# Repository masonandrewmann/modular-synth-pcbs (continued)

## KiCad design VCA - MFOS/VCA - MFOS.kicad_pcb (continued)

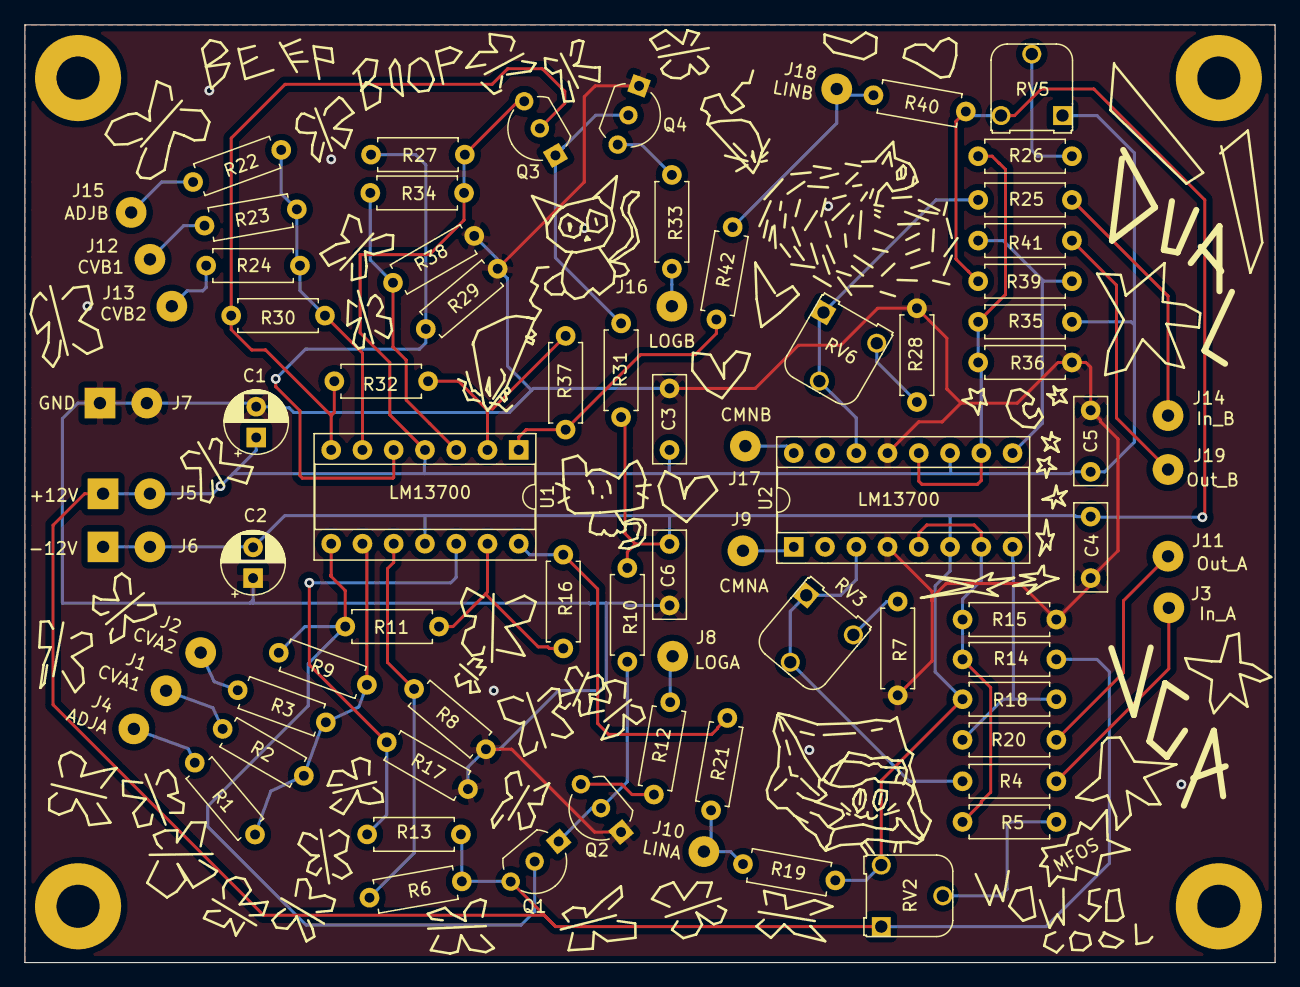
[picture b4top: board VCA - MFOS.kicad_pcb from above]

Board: 2 copper layers, 101.6 x 76.2 mm, 77 parts (0 on the bottom side), 45 nets.

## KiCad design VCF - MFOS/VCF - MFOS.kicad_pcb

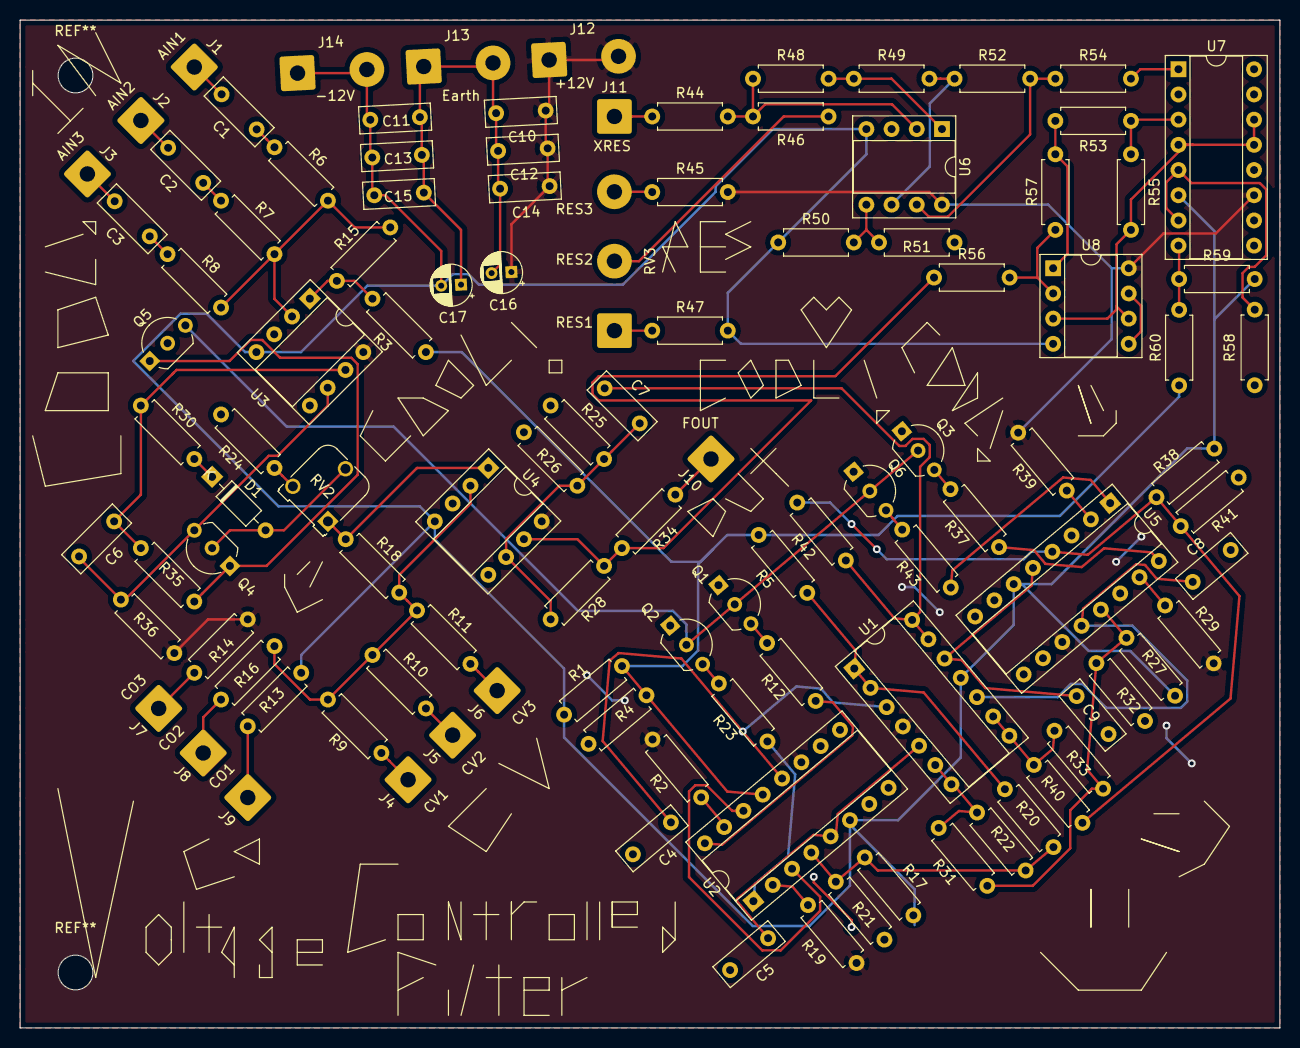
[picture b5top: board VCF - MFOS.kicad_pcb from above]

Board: 2 copper layers, 127.0 x 101.6 mm, 108 parts (0 on the bottom side), 69 nets.

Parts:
C1, C2, C3, C7, C10, C11, C12, C13, C14, C15: 0.1uF; C_Rect_L7.0mm_W2.5mm_P5.00mm
C4, C5, C6, C8, C9: 100pF; C_Rect_L7.0mm_W2.5mm_P5.00mm
C16, C17: 10uF; CP_Radial_D4.0mm_P2.00mm
D1: 1N914; D_DO-35_SOD27_P7.62mm_Horizontal
J1: AIN1; SolderWire-0.75sqmm_1x01_D1.25mm_OD3.5mm
J2: AIN2; SolderWire-0.75sqmm_1x01_D1.25mm_OD3.5mm
J3: AIN3; SolderWire-0.75sqmm_1x01_D1.25mm_OD3.5mm
J4: CV1; SolderWire-0.75sqmm_1x01_D1.25mm_OD3.5mm
J5: CV2; SolderWire-0.75sqmm_1x01_D1.25mm_OD3.5mm
J6: CV3; SolderWire-0.75sqmm_1x01_D1.25mm_OD3.5mm
J7: CO3; SolderWire-0.75sqmm_1x01_D1.25mm_OD3.5mm
J8: CO2; SolderWire-0.75sqmm_1x01_D1.25mm_OD3.5mm
J9: C01; SolderWire-0.75sqmm_1x01_D1.25mm_OD3.5mm
J10: FOUT; SolderWire-0.75sqmm_1x01_D1.25mm_OD3.5mm
J11: XRES; SolderWire-0.75sqmm_1x01_D1.25mm_OD3.5mm
J12: +12V; SolderWire-0.75sqmm_1x02_P7mm_D1.25mm_OD3.5mm
J13: GND; SolderWire-0.75sqmm_1x02_P7mm_D1.25mm_OD3.5mm
J14: -12V; SolderWire-0.75sqmm_1x02_P7mm_D1.25mm_OD3.5mm
Q1, Q2, Q3, Q6: 2N3906; TO-92_Inline_Wide
Q4, Q5: 2N3904; TO-92_Inline_Wide
R1, R13, R17: 39K; R_Axial_DIN0207_L6.3mm_D2.5mm_P7.62mm_Horizontal
R2, R19, R29, R39: 20K; R_Axial_DIN0207_L6.3mm_D2.5mm_P7.62mm_Horizontal
R3, R5, R9, R10, R11, R16, R20, R22, R26, R28, R31, R33, R40, R42, R44, R46, R49, R50, R52: 100K; R_Axial_DIN0207_L6.3mm_D2.5mm_P7.62mm_Horizontal
R4, R21, R32, R41: 100; R_Axial_DIN0207_L6.3mm_D2.5mm_P7.62mm_Horizontal
R6, R7, R8, R36: 1M; R_Axial_DIN0207_L6.3mm_D2.5mm_P7.62mm_Horizontal
R12, R23, R35, R37, R43: 10K; R_Axial_DIN0207_L6.3mm_D2.5mm_P7.62mm_Horizontal
R14: 33K; R_Axial_DIN0207_L6.3mm_D2.5mm_P7.62mm_Horizontal
R15: 390K; R_Axial_DIN0207_L6.3mm_D2.5mm_P7.62mm_Horizontal
R18, R34: 2K; R_Axial_DIN0207_L6.3mm_D2.5mm_P7.62mm_Horizontal
R24: 475; R_Axial_DIN0207_L6.3mm_D2.5mm_P7.62mm_Horizontal
R25: 4.7M; R_Axial_DIN0207_L6.3mm_D2.5mm_P7.62mm_Horizontal
R27, R38: 43K; R_Axial_DIN0207_L6.3mm_D2.5mm_P7.62mm_Horizontal
R30: 47K; R_Axial_DIN0207_L6.3mm_D2.5mm_P7.62mm_Horizontal
R45, R47: 49.9K; R_Axial_DIN0207_L6.3mm_D2.5mm_P7.62mm_Horizontal
R48, R57: 120K; R_Axial_DIN0207_L6.3mm_D2.5mm_P7.62mm_Horizontal
R51, R54, R56, R58: 30K; R_Axial_DIN0207_L6.3mm_D2.5mm_P7.62mm_Horizontal
R53: 200K; R_Axial_DIN0207_L6.3mm_D2.5mm_P7.62mm_Horizontal
R55: 1K; R_Axial_DIN0207_L6.3mm_D2.5mm_P7.62mm_Horizontal
R59: 4.7K; R_Axial_DIN0207_L6.3mm_D2.5mm_P7.62mm_Horizontal
R60: 150K; R_Axial_DIN0207_L6.3mm_D2.5mm_P7.62mm_Horizontal
RV2: 100; Potentiometer_Runtron_RM-065_Vertical
RV3: 100K; SolderWire-0.75sqmm_1x03_P7mm_D1.25mm_OD3.5mm
U1: TL084; DIP-14_W7.62mm_Socket
U2, U5, U7: LM13700; DIP-16_W7.62mm_Socket
U3, U4, U6, U8: TL082; DIP-8_W7.62mm_Socket

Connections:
+12V: C10.1, C12.1, C14.1, C16.1, J12.1, J12.2, R2.2, R14.2, R19.2, R29.2, R36.2, R39.2, R45.2, U1.4, U2.11, U3.8, U4.8, U5.11, U6.8, U7.11, U8.8
-12V: C11.2, C13.2, C15.2, C17.2, J14.1, J14.2, R1.1, R13.1, R17.1, R27.1, R38.1, R47.2, R50.1, R59.2, U1.11, U2.6, U3.4, U4.4, U5.6, U6.4, U7.6, U8.4
Earth: C4.2, C5.2, C8.2, C9.2, C10.2, C11.1, C12.2, C13.1, C14.2, C15.1, C16.2, C17.1, J13.1, J13.2, Q1.1, Q2.1, Q3.1, Q5.2, Q6.1, R4.1, R21.1, R24.2, R25.1, R26.2, R32.1, R41.1, R51.2, R55.2, R58.2, U2.3, U2.14, U3.3, U3.5, U4.3, U4.5, U5.3, U5.14, U6.3, U7.4, U7.13, U7.14, U8.3, U8.6
unnamed: C1.1, R6.1
unnamed: C1.2, J1.1
unnamed: C2.1, R7.1
unnamed: C2.2, J2.1
unnamed: C3.1, R8.1
unnamed: C3.2, J3.1
unnamed: C4.1, U1.3, U2.12
unnamed: C5.1, U1.5, U2.5
unnamed: C6.1, R30.1, R35.2, U3.7
unnamed: C6.2, Q4.3, R36.1, U3.6
unnamed: C7.1, R42.1, U1.13, U1.14
unnamed: C7.2, R25.2, R26.1, R28.2, U4.6
unnamed: C8.1, U1.10, U5.12
unnamed: C9.1, U1.12, U5.5
unnamed: D1.1, R30.2
unnamed: D1.2, Q4.2, RV2.2
unnamed: J4.1, R9.1
unnamed: J5.1, R10.2
unnamed: J6.1, R11.2
unnamed: J7.1, R14.1
unnamed: J8.1, R16.2
unnamed: J9.1, R13.2
unnamed: J10.1, R34.1
unnamed: J11.1, R44.1
unnamed: Q1.2, Q2.2, Q3.2, Q5.3, Q6.2
unnamed: Q1.3, R12.2
unnamed: Q2.3, R23.2
unnamed: Q3.3, R37.2
unnamed: Q4.1, Q5.1, R35.1
unnamed: Q6.3, R43.2
unnamed: R2.1, U2.15
unnamed: R9.2, R10.1, R11.1, R16.1, R18.2, U4.2
unnamed: R12.1, U2.16
unnamed: R3.2, R15.1, U3.1
unnamed: R6.2, R7.2, R8.2, R15.2, U3.2
unnamed: R17.2, R20.1, R21.2, R22.2, U2.4
unnamed: R18.1, RV2.1, U4.1
unnamed: R19.1, U2.2
unnamed: R5.1, R20.2, U1.1, U1.2
unnamed: R22.1, R31.2, U1.6, U1.7
unnamed: R23.1, U2.1
unnamed: R24.1, RV2.3
unnamed: R27.2, R31.1, R32.2, R33.2, U5.13
unnamed: R29.1, U5.15
unnamed: R33.1, R40.2, U1.8, U1.9
unnamed: R37.1, U5.16
unnamed: R38.2, R40.1, R41.2, R42.2, U5.4
unnamed: R39.1, U5.2
unnamed: R43.1, U5.1
unnamed: R44.2, R46.2, R48.1, U6.2
unnamed: R45.1, RV3.3
unnamed: R46.1, RV3.2
unnamed: R47.1, RV3.1
unnamed: R48.2, R49.1, U6.1
unnamed: R49.2, R52.1, U6.6
unnamed: R50.2, R51.1, U6.5
unnamed: R52.2, R54.1, U6.7
unnamed: R53.1, R57.2, U8.1
unnamed: R53.2, R55.1, U7.3
unnamed: R54.2, U7.1
unnamed: R56.2, R57.1, U8.2
unnamed: R58.1, U7.5, U7.7
unnamed: R59.1, R60.2, U7.8
unnamed: U8.5, U8.7
RA: R28.1, R34.2, R56.1, U4.7
RB: R1.2, R3.1, R4.2, R5.2, R60.1, U2.13

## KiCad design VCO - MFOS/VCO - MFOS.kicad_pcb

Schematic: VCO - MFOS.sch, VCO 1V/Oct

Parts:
C1, C2, C5: 100pF; C_Rect_L7.0mm_W2.5mm_P5.00mm
C3: 0.005uF; C_Radial_D8.0mm_H7.0mm_P3.50mm
C4: 0.001uF; C_Rect_L7.0mm_W2.5mm_P5.00mm
C6: 4.7pF; C_Rect_L7.0mm_W2.5mm_P5.00mm
C7: 0.1uF; C_Rect_L7.0mm_W2.5mm_P5.00mm
D1, D2: D; D_T-1_P5.08mm_Horizontal
J1: CV1; SolderWirePad_1x01_Drill1mm
J2: CV2; SolderWirePad_1x01_Drill1mm
J3: CV3; SolderWirePad_1x01_Drill1mm
J4: CV4; SolderWirePad_1x01_Drill1mm
J5: LIN; SolderWirePad_1x01_Drill1mm
J6: SYNC; SolderWirePad_1x01_Drill1mm
J12: RV1P2; SolderWirePad_1x01_Drill1mm
J13: RV2P2; SolderWirePad_1x01_Drill1mm
J14: RV1P1; SolderWirePad_1x01_Drill1mm
J15: RV2P1; SolderWirePad_1x01_Drill1mm
J16: RV2P3; SolderWirePad_1x01_Drill1mm
J17: RV1P3; SolderWirePad_1x01_Drill1mm
J24: R11_inv; SolderWirePad_1x01_Drill1mm
J25: R11_out; SolderWirePad_1x01_Drill1mm
Q1: SSM2210; DIP-8_W7.62mm_Socket
Q2: Q_PJFET_DSG; TO-92L_Inline_Wide
R1, R9: 200k; R_Axial_DIN0207_L6.3mm_D2.5mm_P7.62mm_Horizontal
R2: 10k; R_Axial_DIN0207_L6.3mm_D2.5mm_P7.62mm_Horizontal
R3, R14, R17, R25: 1M; R_Axial_DIN0207_L6.3mm_D2.5mm_P7.62mm_Horizontal
R4, R5, R6, R7, R8: 100k; R_Axial_DIN0207_L6.3mm_D2.5mm_P7.62mm_Horizontal
R10: 47k; R_Axial_DIN0207_L6.3mm_D2.5mm_P7.62mm_Horizontal
R11: 2k; R_Axial_DIN0207_L6.3mm_D2.5mm_P7.62mm_Horizontal
R12: 475; R_Axial_DIN0207_L6.3mm_D2.5mm_P7.62mm_Horizontal
R13, R18, R20: 100K; R_Axial_DIN0207_L6.3mm_D2.5mm_P7.62mm_Horizontal
R15: 4.7K; R_Axial_DIN0207_L6.3mm_D2.5mm_P7.62mm_Horizontal
R16, R21, R23: 10K; R_Axial_DIN0207_L6.3mm_D2.5mm_P7.62mm_Horizontal
R19: 18k; R_Axial_DIN0207_L6.3mm_D2.5mm_P7.62mm_Horizontal
R22: 1K; R_Axial_DIN0207_L6.3mm_D2.5mm_P7.62mm_Horizontal
R24: 2K; R_Axial_DIN0207_L6.3mm_D2.5mm_P7.62mm_Horizontal
RV1, RV2: 100k; SolderWirePad_1x03_P3.175mm_Drill1mm
RV3: 100; Potentiometer_Runtron_RM-065_Vertical
RV4: 100K; Potentiometer_Runtron_RM-065_Vertical
U1: OP275; DIP-8_W7.62mm_Socket
U2: TL072; DIP-8_W7.62mm_Socket

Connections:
+12V: C7.1, R9.1, R10.1, R17.1, R23.1, U1.8 (V+), U2.8 (V+); also elsewhere on the board
-12V: R1.2, R2.2, R19.2, U1.4 (V-), U2.4 (V-); also elsewhere on the board
Earth: C5.2, C7.2, Q1.2 (B1), R12.2, R13.1, R20.2, R24.1, U1.3 (+), U1.5 (+), U2.3 (+); also elsewhere on the board
unnamed: C1.1, J24.1, R3.1, R4.1, R5.1, R6.1, R7.1, R8.1, R11.2, U1.2 (-)
unnamed: C1.2, J25.1, R11.1, RV3.1, U1.1
unnamed: C2.1, Q1.8 (C2), R14.1, R17.2, U1.6 (-)
unnamed: C2.2, R16.1, RV4.3, U1.7
unnamed: C3.1, Q1.1 (C1), Q2.1, U2.2 (-)
unnamed: C4.1, J6.1, R20.1
unnamed: C4.2, R22.2
unnamed: C5.1, D2.1 (K), R18.1, R19.1
unnamed: C6.1, R21.1, R25.2, U2.5 (+)
unnamed: C6.2, D2.2 (A), R25.1, U2.7
unnamed: D1.1 (K), R15.2
unnamed: D1.2 (A), Q1.7 (B2), RV3.2
unnamed: J1.1, R5.2
unnamed: J2.1, R6.2
unnamed: J3.1, R7.2
unnamed: J4.1, R8.2
unnamed: J5.1, R13.2, R14.2
unnamed: J12.1, R4.2, RV1.2
unnamed: J13.1, R3.2, RV2.2
unnamed: J14.1, R2.1, RV1.1
unnamed: J15.1, R1.1, RV2.1
unnamed: J16.1, R9.2, RV2.3
unnamed: J17.1, R10.2, RV1.3
unnamed: Q1.3 (E1), Q1.6 (E2), R16.2
unnamed: Q2.3, R18.2
unnamed: R12.1, RV3.3
unnamed: R15.1, RV4.1, RV4.2
unnamed: R22.1, R23.2, R24.2, U2.6 (-)
RAW: C3.2, Q2.2, R21.2, U2.1; also elsewhere on the board

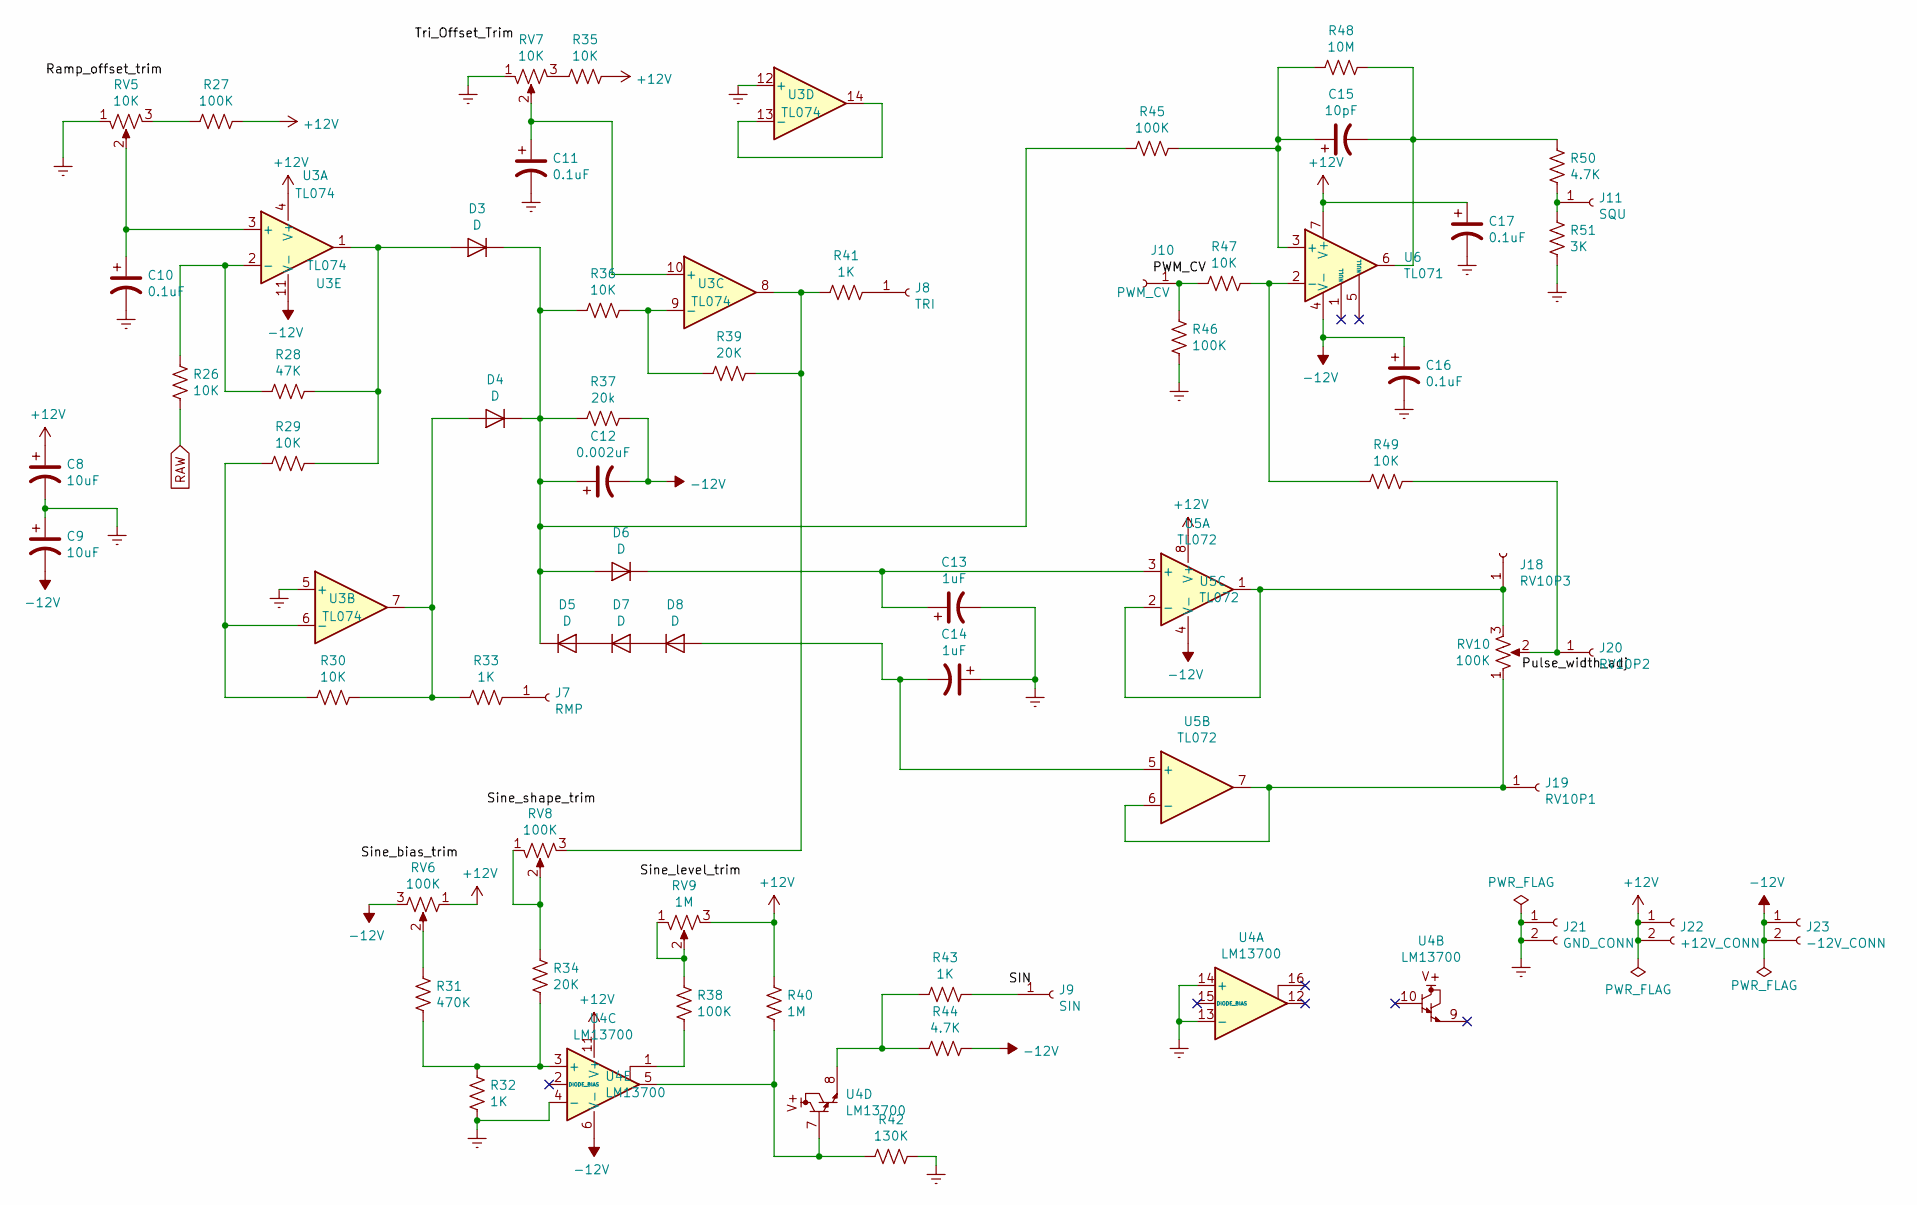
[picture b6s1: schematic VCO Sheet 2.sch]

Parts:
C8, C9: 10uF; CP_Radial_D5.0mm_P2.50mm
C10, C11, C16, C17: 0.1uF; C_Rect_L7.0mm_W2.5mm_P5.00mm
C12: 0.002uF; C_Rect_L7.0mm_W2.5mm_P5.00mm
C13, C14: 1uF; CP_Radial_D4.0mm_P2.00mm
C15: 10pF; C_Rect_L7.0mm_W2.5mm_P5.00mm
D3, D4, D5, D6, D7, D8: D; D_T-1_P5.08mm_Horizontal
J7: RMP; SolderWirePad_1x01_Drill1mm
J8: TRI; SolderWirePad_1x01_Drill1mm
J9: SIN; SolderWirePad_1x01_Drill1mm
J10: PWM_CV; SolderWirePad_1x01_Drill1mm
J11: SQU; SolderWirePad_1x01_Drill1mm
J18: RV10P3; SolderWirePad_1x01_Drill1mm
J19: RV10P1; SolderWirePad_1x01_Drill1mm
J20: RV10P2; SolderWirePad_1x01_Drill1mm
J21: GND_CONN; SolderWirePad_1x02_P3.81mm_Drill1mm
J22: +12V_CONN; SolderWirePad_1x02_P3.81mm_Drill1mm
J23: -12V_CONN; SolderWirePad_1x02_P3.81mm_Drill1mm
R26, R29, R30, R35, R36, R47, R49: 10K; R_Axial_DIN0207_L6.3mm_D2.5mm_P7.62mm_Horizontal
R27, R38, R45, R46: 100K; R_Axial_DIN0207_L6.3mm_D2.5mm_P7.62mm_Horizontal
R28: 47K; R_Axial_DIN0207_L6.3mm_D2.5mm_P7.62mm_Horizontal
R31: 470K; R_Axial_DIN0207_L6.3mm_D2.5mm_P7.62mm_Horizontal
R32, R33, R41, R43: 1K; R_Axial_DIN0207_L6.3mm_D2.5mm_P7.62mm_Horizontal
R34, R39: 20K; R_Axial_DIN0207_L6.3mm_D2.5mm_P7.62mm_Horizontal
R37: 20k; R_Axial_DIN0207_L6.3mm_D2.5mm_P7.62mm_Horizontal
R40: 1M; R_Axial_DIN0207_L6.3mm_D2.5mm_P7.62mm_Horizontal
R42: 130K; R_Axial_DIN0207_L6.3mm_D2.5mm_P7.62mm_Horizontal
R44, R50: 4.7K; R_Axial_DIN0207_L6.3mm_D2.5mm_P7.62mm_Horizontal
R48: 10M; R_Axial_DIN0207_L6.3mm_D2.5mm_P7.62mm_Horizontal
R51: 3K; R_Axial_DIN0207_L6.3mm_D2.5mm_P7.62mm_Horizontal
RV5, RV7: 10K; Potentiometer_Runtron_RM-065_Vertical
RV6, RV8: 100K; Potentiometer_Runtron_RM-065_Vertical
RV9: 1M; Potentiometer_Runtron_RM-065_Vertical
RV10: 100K; SolderWirePad_1x03_P3.175mm_Drill1mm
U3: TL074; DIP-14_W7.62mm_Socket
U4: LM13700; DIP-16_W7.62mm_Socket
U5: TL072; DIP-8_W7.62mm_Socket
U6: TL071; DIP-8_W7.62mm_Socket

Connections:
+12V: C8.1, C17.1, J22.1, J22.2, R27.2, R35.1, R40.1, RV6.1, RV9.3, U3.4 (V+), U4.11 (V+), U5.8 (V+), U6.7 (V+); also elsewhere on the board
-12V: C9.2, C12.2, C16.1, J23.1, J23.2, R37.1, R44.1, RV6.3, U3.11 (V-), U4.6 (V-), U5.4 (V-), U6.4 (V-); also elsewhere on the board
Earth: C8.2, C9.1, C10.2, C11.2, C13.2, C14.1, C16.2, C17.2, J21.1, J21.2, R32.2, R42.1, R46.2, R51.2, RV5.1, RV7.1, U3.5 (+), U3.12 (+), U4.4 (-), U4.13 (-), U4.14 (+); also elsewhere on the board
unnamed: C10.1, RV5.2, U3.3 (+)
unnamed: C11.1, RV7.2, U3.10 (+)
unnamed: C12.1, D3.1 (K), D4.1 (K), D5.1 (K), D6.2 (A), R36.2, R37.2, R45.2
unnamed: C13.1, D6.1 (K), U5.3 (+)
unnamed: C14.2, D8.2 (A), U5.5 (+)
unnamed: C15.1, R45.1, R48.2, U6.3 (+)
unnamed: C15.2, R48.1, R50.1, U6.6
unnamed: D3.2 (A), R28.1, R29.1, U3.1
unnamed: D4.2 (A), R30.1, R33.2, U3.7
unnamed: D5.2 (A), D7.1 (K)
unnamed: D7.2 (A), D8.1 (K)
unnamed: J7.1, R33.1
unnamed: J8.1, R41.1
unnamed: J9.1, R43.1
unnamed: J10.1, R46.1, R47.2
unnamed: J11.1, R50.2, R51.1
unnamed: J18.1, RV10.3, U5.1, U5.2 (-)
unnamed: J19.1, RV10.1, U5.6 (-), U5.7
unnamed: J20.1, R49.1, RV10.2
unnamed: R26.1, R28.2, U3.2 (-)
unnamed: R27.1, RV5.3
unnamed: R29.2, R30.2, U3.6 (-)
unnamed: R31.1, RV6.2
unnamed: R31.2, R32.1, R34.2, U4.3 (+)
unnamed: R34.1, RV8.1, RV8.2
unnamed: R35.2, RV7.3
unnamed: R36.1, R39.1, U3.9 (-)
unnamed: R38.1, RV9.1, RV9.2
unnamed: R38.2, U4.1
unnamed: R39.2, R41.2, RV8.3, U3.8
unnamed: R40.2, R42.2, U4.5, U4.7
unnamed: R43.2, R44.2, U4.8
unnamed: R47.1, R49.2, U6.2 (-)
unnamed: U3.13 (-), U3.14
RAW: R26.2; also elsewhere on the board

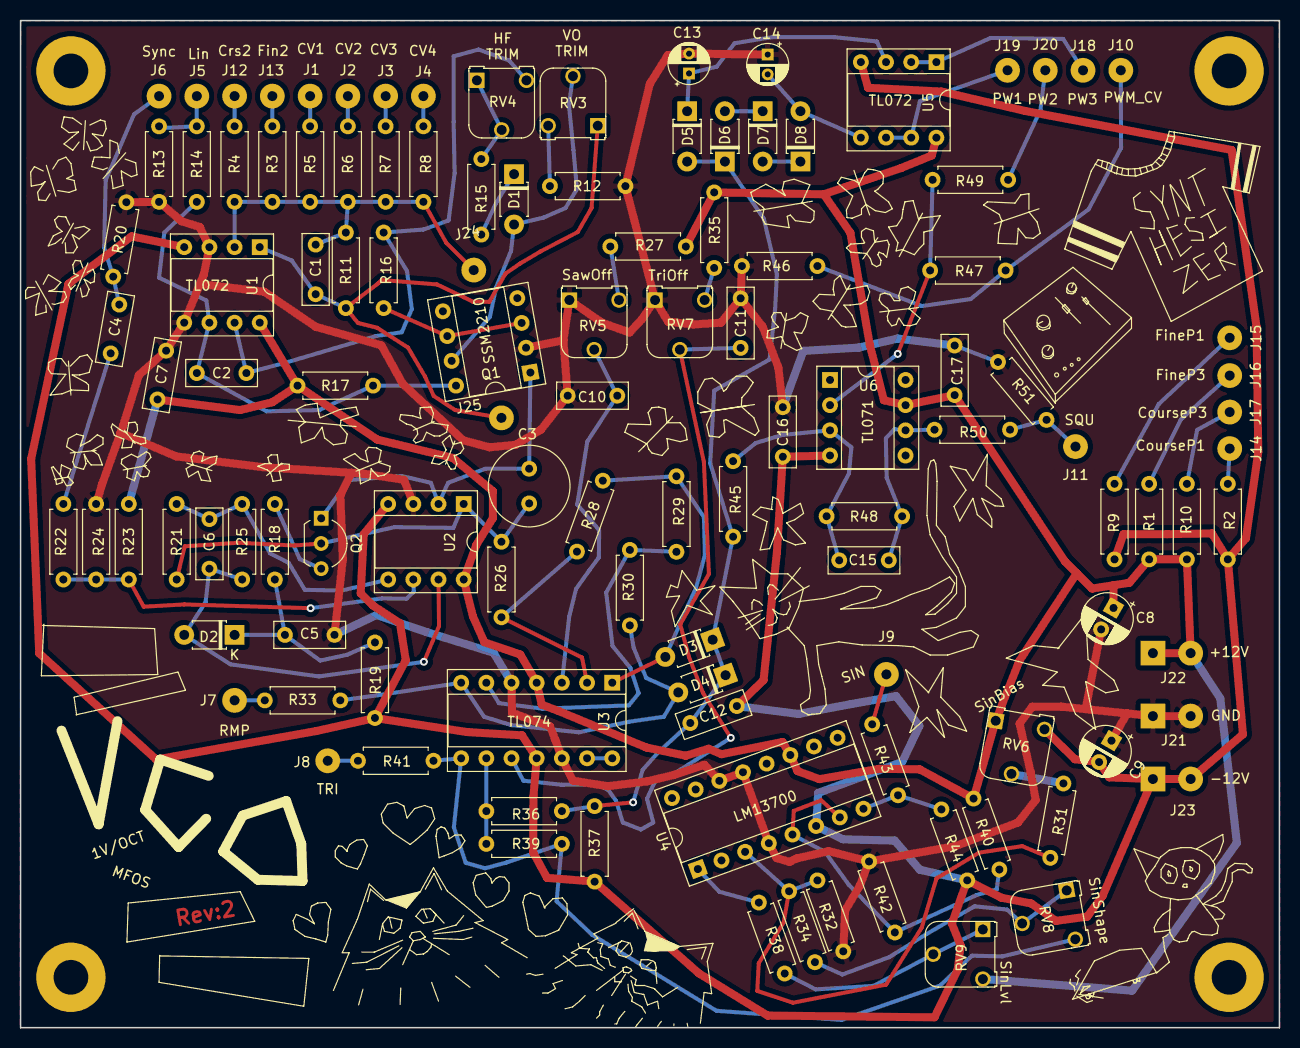
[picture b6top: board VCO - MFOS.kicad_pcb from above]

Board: 2 copper layers, 127.0 x 101.6 mm, 116 parts (0 on the bottom side), 66 nets.
